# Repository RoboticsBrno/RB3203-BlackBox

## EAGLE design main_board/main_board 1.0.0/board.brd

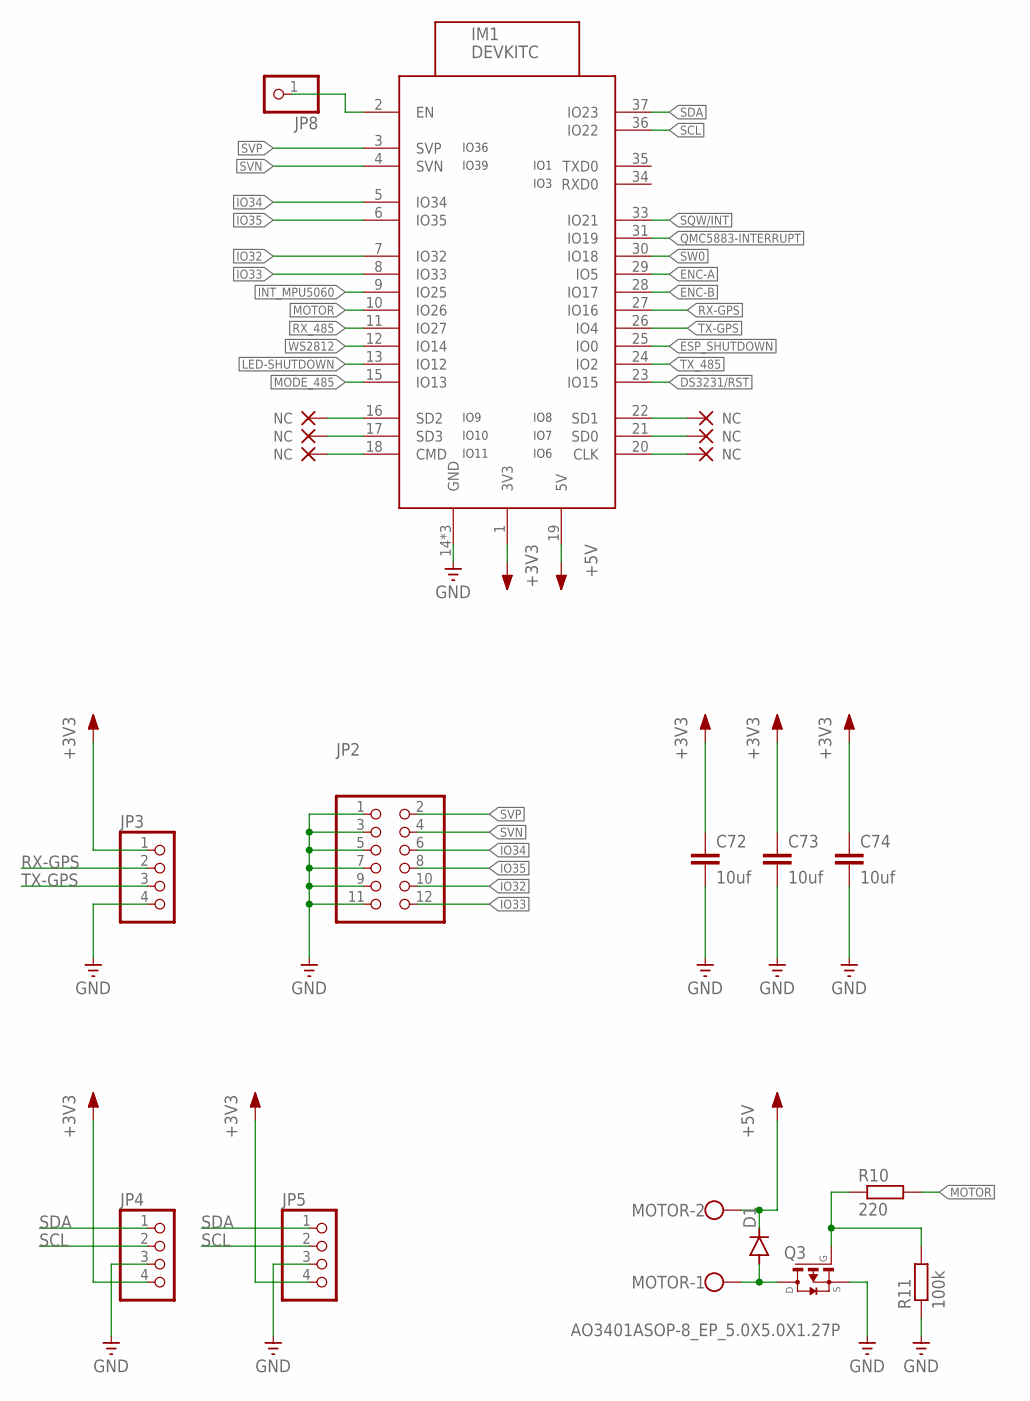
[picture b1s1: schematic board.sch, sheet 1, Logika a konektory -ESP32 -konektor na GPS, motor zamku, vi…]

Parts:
C72, C73, C74: 10uf; C0402
D1: DIODE-DO214BA; DO214BA
IM1: DEVKITC
JP2: PINHD-2X6; 2X06
JP3, JP4, JP5: PINHD-1X4; 1X04
JP8: PINHD-1X1; 1X01
MOTOR: W237-102
Q3: AO3401ASOP-8_EP_5.0X5.0X1.27P; SOP-8_EP_5.0X5.0X1.27P
R10: 220; R0402
R11: 100k; R0402

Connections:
+3V3: C72.1, C73.1, C74.1, IM1.1 (3V3), JP3.1, JP4.4, JP5.4; also elsewhere on the board
+5V: D1.C, IM1.19 (5V), MOTOR.2; also elsewhere on the board
DS3231/RST: IM1.23 (IO15); also elsewhere on the board
ENC-A: IM1.29 (IO5); also elsewhere on the board
ENC-B: IM1.28 (IO17); also elsewhere on the board
ESP_SHUTDOWN: IM1.25 (IO0); also elsewhere on the board
GND: C72.2, C73.2, C74.2, IM1.14 (GND), IM1.32 (GND), IM1.38 (GND), JP2.1, JP2.3, JP2.5, JP2.7, JP2.9, JP2.11, JP3.4, JP4.3, JP5.3, Q3.1 (S), Q3.2 (S), Q3.3 (S), R11.1; also elsewhere on the board
INT_MPU5060: IM1.9 (IO25); also elsewhere on the board
IO9_NC: IM1.16 (SD2)
IO9_NC1: IM1.20 (CLK)
IO10_NC: IM1.17 (SD3)
IO10_NC1: IM1.21 (SD0)
IO11_NC: IM1.18 (CMD)
IO11_NC1: IM1.22 (SD1)
IO32: IM1.7 (IO32), JP2.10
IO33: IM1.8 (IO33), JP2.12
IO34: IM1.5 (IO34), JP2.6
IO35: IM1.6 (IO35), JP2.8
LED-SHUTDOWN: IM1.13 (IO12); also elsewhere on the board
MODE_485: IM1.15 (IO13); also elsewhere on the board
MOTOR: IM1.10 (IO26), R10.2
unnamed: D1.A, MOTOR.1, Q3.5 (D), Q3.6 (D), Q3.7 (D), Q3.8 (D), Q3.9 (D)
unnamed: IM1.2 (EN), JP8.1
unnamed: Q3.4 (G), R10.1, R11.2
QMC5883-INTERRUPT: IM1.31 (IO19); also elsewhere on the board
RX-GPS: IM1.27 (IO16), JP3.2
RX_485: IM1.11 (IO27); also elsewhere on the board
SCL: IM1.36 (IO22), JP4.2, JP5.2; also elsewhere on the board
SDA: IM1.37 (IO23), JP4.1, JP5.1; also elsewhere on the board
SQW/INT: IM1.33 (IO21); also elsewhere on the board
SVN: IM1.4 (SVN), JP2.4
SVP: IM1.3 (SVP), JP2.2
SW0: IM1.30 (IO18); also elsewhere on the board
TX-GPS: IM1.26 (IO4), JP3.3
TX_485: IM1.24 (IO2); also elsewhere on the board
WS2812: IM1.12 (IO14); also elsewhere on the board

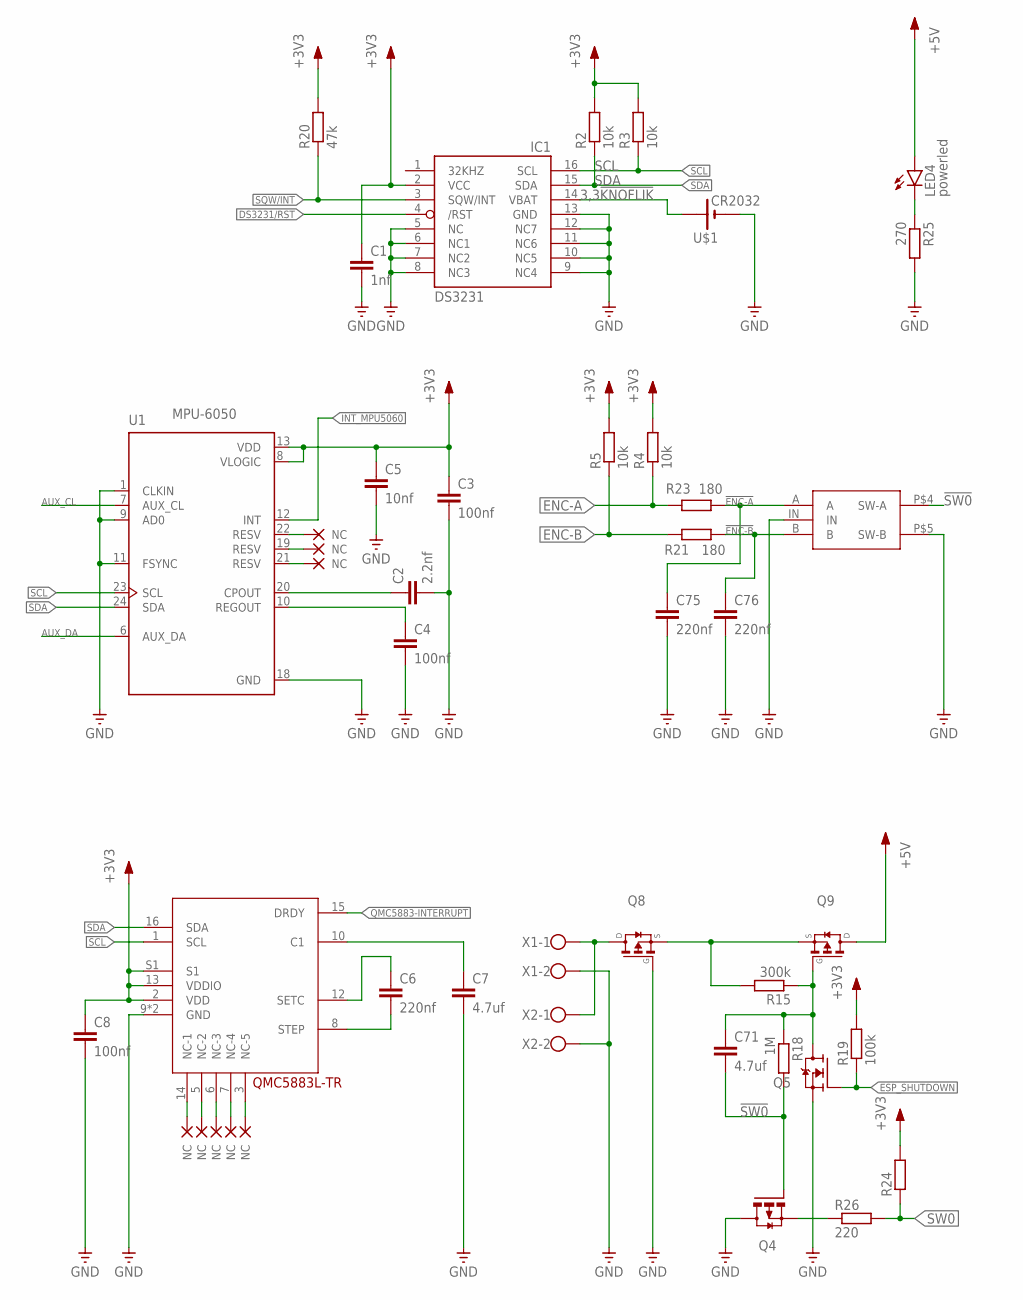
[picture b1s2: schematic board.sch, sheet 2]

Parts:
C1: 1nf; C0402
C2: 2.2nf; C0402
C3: 100nf; C0402
C4: 100nf; C0402K
C5: 10nf; C0402
C6, C75, C76: 220nf; C0402
C7: 4.7uf; C0402
C8: 100nf; C0402P
C71: 4.7uf; C0603
IC1: DS3231/SO; SO16W
IC2: QMC5883L-TR; QMC5882L-TR
LED4: powerled; SML0603
Q4: BSS84; SOT23
Q5: N-MOSFET-SOT23-GSD; SOT23
Q8, Q9: AO3401ASOP-8_EP_5.0X5.0X1.27P; SOP-8_EP_5.0X5.0X1.27P
R2, R3, R4, R5: 10k; R0402
R15: 300k; R0603
R18: 1M; R0603
R19: 100k; R0402
R20, R24: 47k; R0402
R21, R23: 180; R0402
R25: 270; R0402
R26: 220; R0402
U1: MPU-6050; QFN50P400X400X95-24N
U$1: CR2032; CH075
U$62: EC11-1S
X1, X2: W237-102

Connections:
3,3!KNOFLIK: IC1.14 (VBAT), U$1.+
!ENC-A: C75.1, R23.1, U$62.A
!ENC-B: C76.1, R21.1, U$62.B
!SW0: C71.2, Q4.1 (G), R18.2, U$62.P$4 (SW-A)
+3V3: C1.1, C3.1, C5.1, C8.1, IC1.2 (VCC), IC2.2 (VDD), IC2.13 (VDDIO), IC2.S1, R2.2, R3.2, R4.2, R5.2, R19.2, R20.2, R24.2, U1.8 (VLOGIC), U1.13 (VDD); also elsewhere on the board
+5V: LED4.A, Q9.5 (D), Q9.6 (D), Q9.7 (D), Q9.8 (D), Q9.9 (D); also elsewhere on the board
AUX_CL: U1.7 (AUX_CL)
AUX_DA: U1.6 (AUX_DA)
DS3231/RST: IC1.4 (/RST); also elsewhere on the board
ENC-A: R4.1, R23.2; also elsewhere on the board
ENC-B: R5.1, R21.2; also elsewhere on the board
ESP_SHUTDOWN: Q5.1 (G), R19.1; also elsewhere on the board
GND: C1.2, C2.2, C3.2, C4.2, C5.2, C7.2, C8.2, C75.2, C76.2, IC1.5 (NC), IC1.6 (NC1), IC1.7 (NC2), IC1.8 (NC3), IC1.9 (NC4), IC1.10 (NC5), IC1.11 (NC6), IC1.12 (NC7), IC1.13 (GND), IC2.9 (GND), IC2.11 (GND), Q4.3 (D), Q5.2 (S), Q8.4 (G), R25.2, U1.1 (CLKIN), U1.9 (AD0), U1.11 (FSYNC), U1.18 (GND), U$1.-, U$62.IN, U$62.P$5 (SW-B), X1.2, X2.2; also elsewhere on the board
INT_MPU5060: U1.12 (INT); also elsewhere on the board
IO9_NC2: IC2.5 (NC-2)
IO9_NC3: IC2.14 (NC-1)
IO9_NC4: U1.19 (RESV)
IO9_NC5: U1.21 (RESV)
IO9_NC6: IC2.3 (NC-5)
IO9_NC7: IC2.7 (NC-4)
IO10_NC2: IC2.6 (NC-3)
IO10_NC4: U1.22 (RESV)
LED4: LED4.C, R25.1
unnamed: C2.1, U1.20 (CPOUT)
unnamed: C4.1, U1.10 (REGOUT)
unnamed: Q8.5 (D), Q8.6 (D), Q8.7 (D), Q8.8 (D), Q8.9 (D), X1.1, X2.1
unnamed: Q8.1 (S), Q8.2 (S), Q8.3 (S), Q9.1 (S), Q9.2 (S), Q9.3 (S), R15.2
unnamed: C71.1, Q5.3 (D), Q9.4 (G), R15.1, R18.1
unnamed: Q4.2 (S), R26.1
unnamed: C6.1, IC2.12 (SETC)
unnamed: C6.2, IC2.8 (STEP)
unnamed: C7.1, IC2.10 (C1)
QMC5883-INTERRUPT: IC2.15 (DRDY); also elsewhere on the board
SCL: IC1.16 (SCL), IC2.1 (SCL), R3.1, U1.23 (SCL); also elsewhere on the board
SDA: IC1.15 (SDA), IC2.16 (SDA), R2.1, U1.24 (SDA); also elsewhere on the board
SQW/INT: IC1.3 (SQW/INT), R20.1; also elsewhere on the board
SW0: R24.1, R26.2; also elsewhere on the board

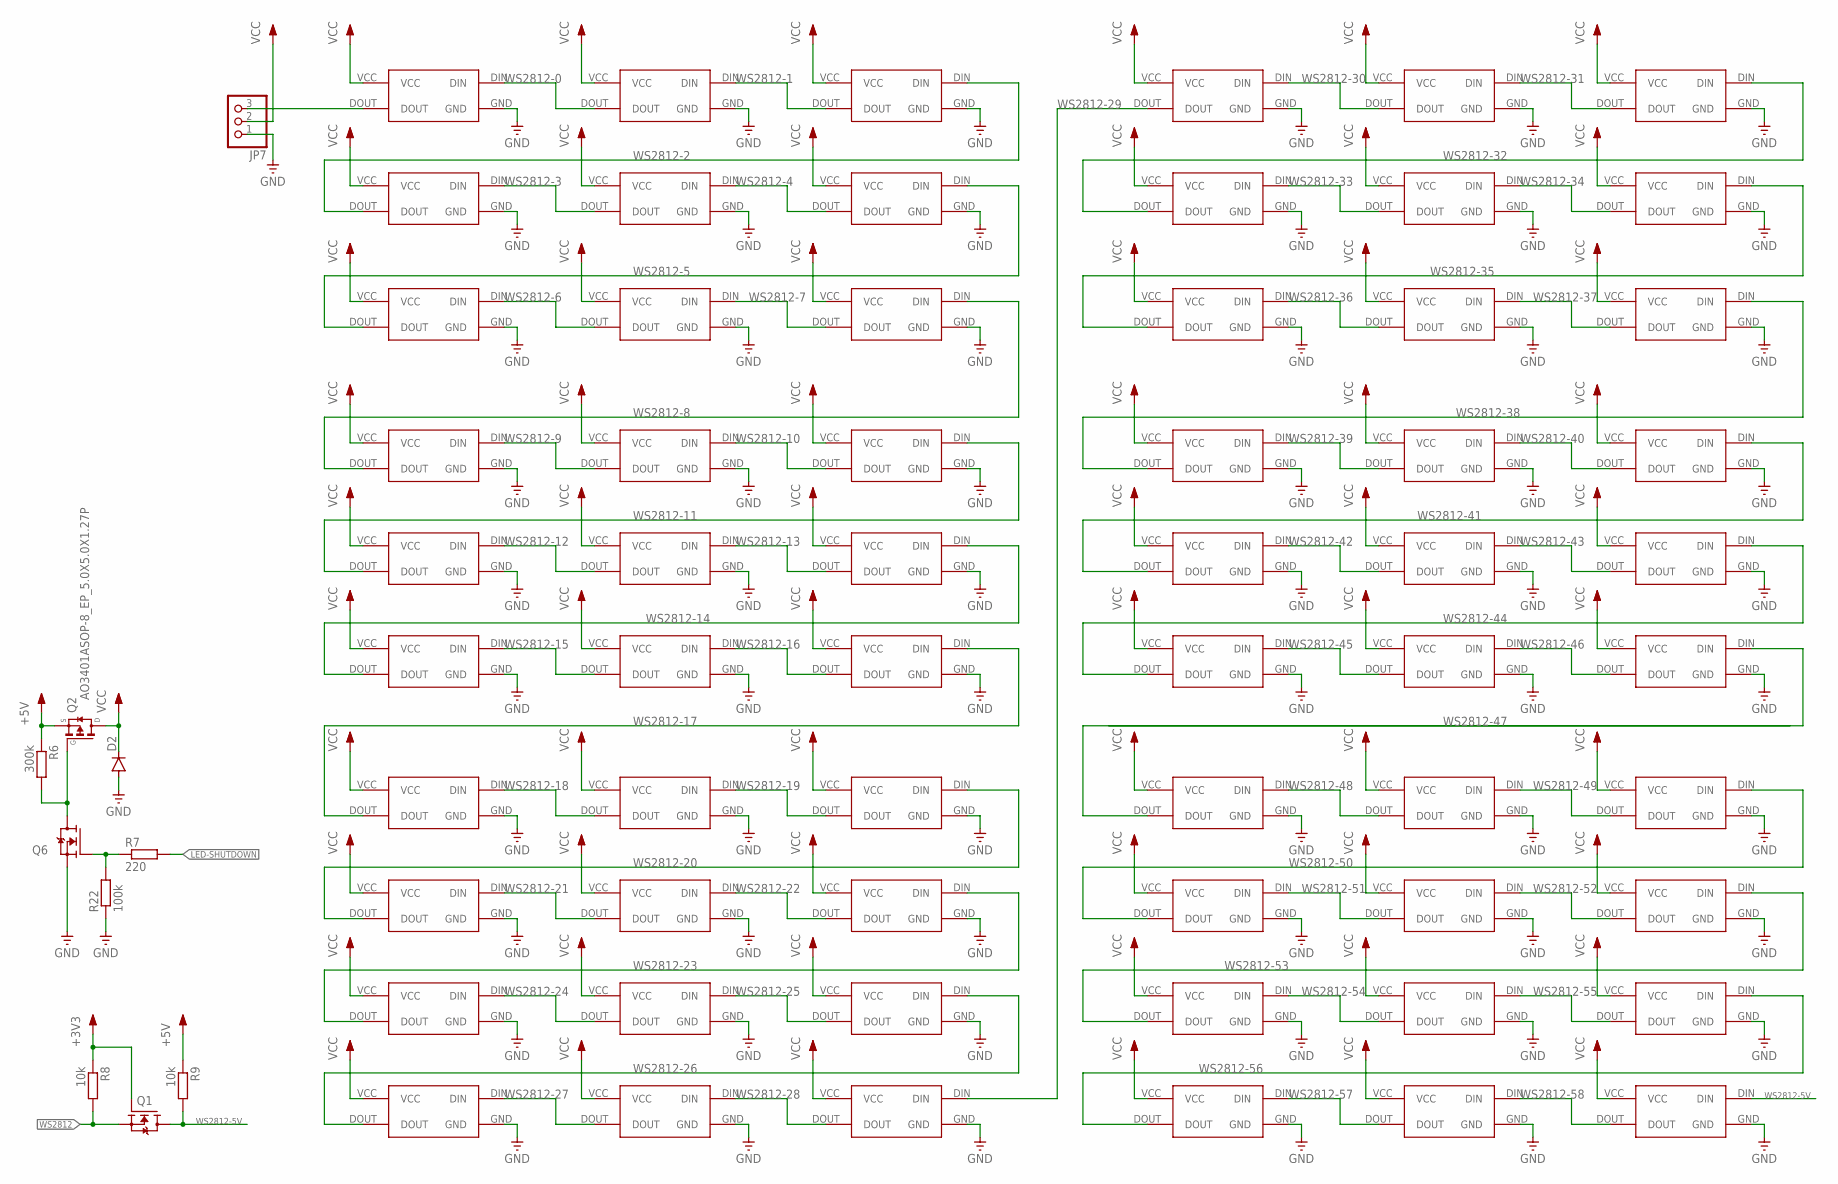
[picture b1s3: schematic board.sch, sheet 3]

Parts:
D2: DIODE-DO214BA; DO214BA
JP7: PINHD-1X3; 1X03
Q1, Q6: N-MOSFET-SOT23-GSD; SOT23
Q2: AO3401ASOP-8_EP_5.0X5.0X1.27P; SOP-8_EP_5.0X5.0X1.27P
R6: 300k; R0402
R7: 220; R0402
R8, R9: 10k; R0402
R22: 100k; R0402
U$2, U$3, U$4, U$5, U$6, U$7, U$8, U$9, U$10, U$11, U$12, U$13, U$14, U$15, U$16, U$17, U$18, U$19, U$20, U$21, U$22, U$23, U$24, U$25, U$26, U$27, U$28, U$29, U$30, U$31, U$32, U$33, U$34, U$35, U$36, U$37, U$38, U$39, U$40, U$41, U$42, U$43, U$44, U$45, U$46, U$47, U$48, U$49, U$50, U$51, U$52, U$53, U$54, U$55, U$56, U$57, U$58, U$59, U$60, U$61: WS2812; WS2812B-MINI

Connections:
+3V3: Q1.1 (G), R8.1; also elsewhere on the board
+5V: Q2.1 (S), Q2.2 (S), Q2.3 (S), R6.1, R9.1; also elsewhere on the board
GND: D2.A, JP7.1, Q6.2 (S), R22.1, U$2.GND, U$3.GND, U$4.GND, U$5.GND, U$6.GND, U$7.GND, U$8.GND, U$9.GND, U$10.GND, U$11.GND, U$12.GND, U$13.GND, U$14.GND, U$15.GND, U$16.GND, U$17.GND, U$18.GND, U$19.GND, U$20.GND, U$21.GND, U$22.GND, U$23.GND, U$24.GND, U$25.GND, U$26.GND, U$27.GND, U$28.GND, U$29.GND, U$30.GND, U$31.GND, U$32.GND, U$33.GND, U$34.GND, U$35.GND, U$36.GND, U$37.GND, U$38.GND, U$39.GND, U$40.GND, U$41.GND, U$42.GND, U$43.GND, U$44.GND, U$45.GND, U$46.GND, U$47.GND, U$48.GND, U$49.GND, U$50.GND, U$51.GND, U$52.GND, U$53.GND, U$54.GND, U$55.GND, U$56.GND, U$57.GND, U$58.GND, U$59.GND, U$60.GND, U$61.GND; also elsewhere on the board
LED-SHUTDOWN: R7.2; also elsewhere on the board
unnamed: JP7.3, U$2.DOUT
unnamed: U$49.DIN, U$50.DOUT
unnamed: Q2.4 (G), Q6.3 (D), R6.2
unnamed: Q6.1 (G), R7.1, R22.2
VCC: D2.C, JP7.2, Q2.5 (D), Q2.6 (D), Q2.7 (D), Q2.8 (D), Q2.9 (D), U$2.VCC, U$3.VCC, U$4.VCC, U$5.VCC, U$6.VCC, U$7.VCC, U$8.VCC, U$9.VCC, U$10.VCC, U$11.VCC, U$12.VCC, U$13.VCC, U$14.VCC, U$15.VCC, U$16.VCC, U$17.VCC, U$18.VCC, U$19.VCC, U$20.VCC, U$21.VCC, U$22.VCC, U$23.VCC, U$24.VCC, U$25.VCC, U$26.VCC, U$27.VCC, U$28.VCC, U$29.VCC, U$30.VCC, U$31.VCC, U$32.VCC, U$33.VCC, U$34.VCC, U$35.VCC, U$36.VCC, U$37.VCC, U$38.VCC, U$39.VCC, U$40.VCC, U$41.VCC, U$42.VCC, U$43.VCC, U$44.VCC, U$45.VCC, U$46.VCC, U$47.VCC, U$48.VCC, U$49.VCC, U$50.VCC, U$51.VCC, U$52.VCC, U$53.VCC, U$54.VCC, U$55.VCC, U$56.VCC, U$57.VCC, U$58.VCC, U$59.VCC, U$60.VCC, U$61.VCC; also elsewhere on the board
WS2812: Q1.2 (S), R8.2; also elsewhere on the board
WS2812-0: U$2.DIN, U$3.DOUT
WS2812-1: U$3.DIN, U$4.DOUT
WS2812-2: U$4.DIN, U$5.DOUT
WS2812-3: U$5.DIN, U$6.DOUT
WS2812-4: U$6.DIN, U$7.DOUT
WS2812-5: U$7.DIN, U$8.DOUT
WS2812-5V: Q1.3 (D), R9.2, U$61.DIN
WS2812-6: U$8.DIN, U$9.DOUT
WS2812-7: U$9.DIN, U$10.DOUT
WS2812-8: U$10.DIN, U$11.DOUT
WS2812-9: U$11.DIN, U$12.DOUT
WS2812-10: U$12.DIN, U$13.DOUT
WS2812-11: U$13.DIN, U$14.DOUT
WS2812-12: U$14.DIN, U$15.DOUT
WS2812-13: U$15.DIN, U$16.DOUT
WS2812-14: U$16.DIN, U$17.DOUT
WS2812-15: U$17.DIN, U$18.DOUT
WS2812-16: U$18.DIN, U$19.DOUT
WS2812-17: U$19.DIN, U$20.DOUT
WS2812-18: U$20.DIN, U$21.DOUT
WS2812-19: U$21.DIN, U$22.DOUT
WS2812-20: U$22.DIN, U$23.DOUT
WS2812-21: U$23.DIN, U$24.DOUT
WS2812-22: U$24.DIN, U$25.DOUT
WS2812-23: U$25.DIN, U$26.DOUT
WS2812-24: U$26.DIN, U$27.DOUT
WS2812-25: U$27.DIN, U$28.DOUT
WS2812-26: U$28.DIN, U$29.DOUT
WS2812-27: U$29.DIN, U$30.DOUT
WS2812-28: U$30.DIN, U$31.DOUT
WS2812-29: U$31.DIN, U$32.DOUT
WS2812-30: U$32.DIN, U$33.DOUT
WS2812-31: U$33.DIN, U$34.DOUT
WS2812-32: U$34.DIN, U$35.DOUT
WS2812-33: U$35.DIN, U$36.DOUT
WS2812-34: U$36.DIN, U$37.DOUT
WS2812-35: U$37.DIN, U$38.DOUT
WS2812-36: U$38.DIN, U$39.DOUT
WS2812-37: U$39.DIN, U$40.DOUT
WS2812-38: U$40.DIN, U$41.DOUT
WS2812-39: U$41.DIN, U$42.DOUT
WS2812-40: U$42.DIN, U$43.DOUT
WS2812-41: U$43.DIN, U$44.DOUT
WS2812-42: U$44.DIN, U$45.DOUT
WS2812-43: U$45.DIN, U$46.DOUT
WS2812-44: U$46.DIN, U$47.DOUT
WS2812-45: U$47.DIN, U$48.DOUT
WS2812-46: U$48.DIN, U$49.DOUT
WS2812-48: U$50.DIN, U$51.DOUT
WS2812-49: U$51.DIN, U$52.DOUT
WS2812-50: U$52.DIN, U$53.DOUT
WS2812-51: U$53.DIN, U$54.DOUT
WS2812-52: U$54.DIN, U$55.DOUT
WS2812-53: U$55.DIN, U$56.DOUT
WS2812-54: U$56.DIN, U$57.DOUT
WS2812-55: U$57.DIN, U$58.DOUT
WS2812-56: U$58.DIN, U$59.DOUT
WS2812-57: U$59.DIN, U$60.DOUT
WS2812-58: U$60.DIN, U$61.DOUT

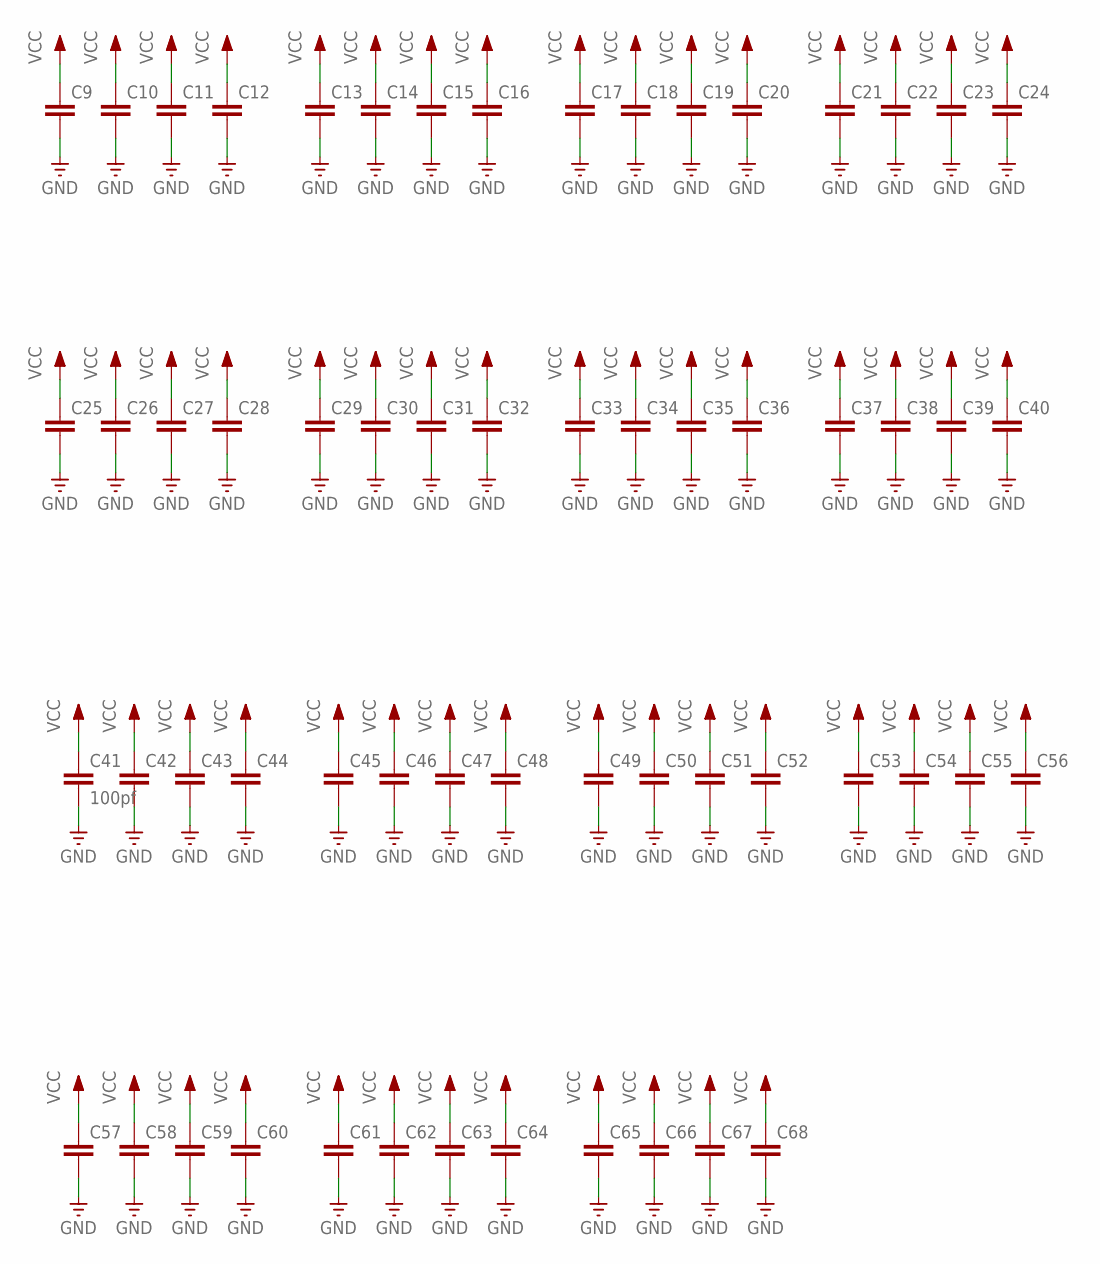
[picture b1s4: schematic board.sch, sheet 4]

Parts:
C9, C10, C11, C12, C13, C14, C15, C16, C17, C18, C19, C20, C21, C22, C23, C24, C25, C26, C27, C28, C29, C30, C31, C32, C33, C34, C35, C36, C37, C38, C39, C40, C42, C43, C44, C45, C46, C47, C48, C49, C50, C51, C52, C53, C54, C55, C56, C57, C58, C59, C60, C61, C62, C63, C64, C65, C66, C67, C68: C-EUC0402; C0402
C41: 100pf; C0402

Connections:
GND: C9.2, C10.2, C11.2, C12.2, C13.2, C14.2, C15.2, C16.2, C17.2, C18.2, C19.2, C20.2, C21.2, C22.2, C23.2, C24.2, C25.2, C26.2, C27.2, C28.2, C29.2, C30.2, C31.2, C32.2, C33.2, C34.2, C35.2, C36.2, C37.2, C38.2, C39.2, C40.2, C41.2, C42.2, C43.2, C44.2, C45.2, C46.2, C47.2, C48.2, C49.2, C50.2, C51.2, C52.2, C53.2, C54.2, C55.2, C56.2, C57.2, C58.2, C59.2, C60.2, C61.2, C62.2, C63.2, C64.2, C65.2, C66.2, C67.2, C68.2; also elsewhere on the board
VCC: C9.1, C10.1, C11.1, C12.1, C13.1, C14.1, C15.1, C16.1, C17.1, C18.1, C19.1, C20.1, C21.1, C22.1, C23.1, C24.1, C25.1, C26.1, C27.1, C28.1, C29.1, C30.1, C31.1, C32.1, C33.1, C34.1, C35.1, C36.1, C37.1, C38.1, C39.1, C40.1, C41.1, C42.1, C43.1, C44.1, C45.1, C46.1, C47.1, C48.1, C49.1, C50.1, C51.1, C52.1, C53.1, C54.1, C55.1, C56.1, C57.1, C58.1, C59.1, C60.1, C61.1, C62.1, C63.1, C64.1, C65.1, C66.1, C67.1, C68.1; also elsewhere on the board

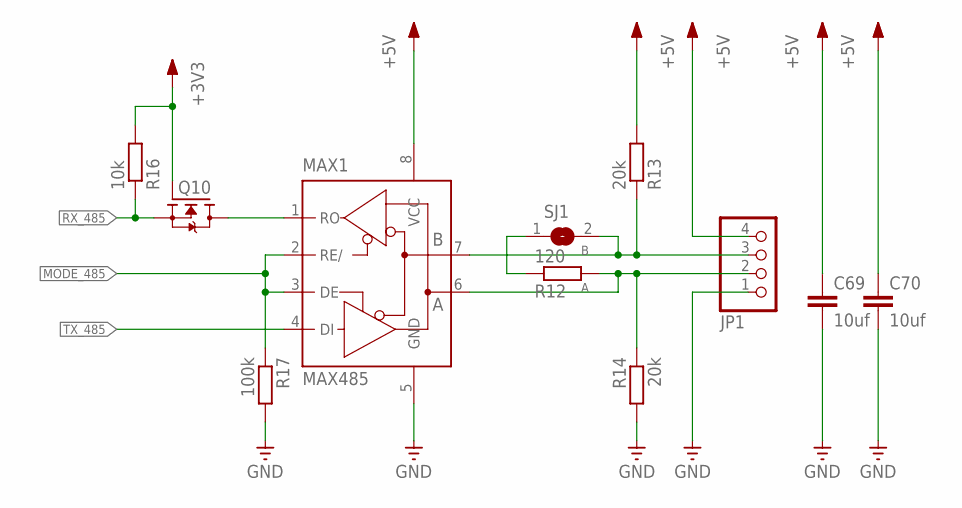
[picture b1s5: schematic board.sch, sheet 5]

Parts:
C69, C70: 10uf; C0402K
JP1: PINHD-1X4; 1X04
MAX1: MAX485; SO08
Q10: N-MOSFET-SOT23-GSD; SOT23
R12: 120; R0402
R13, R14: 20k; R0402
R16: 10k; R0402
R17: 100k; R0402
SJ1: SJ

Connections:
+3V3: Q10.1 (G), R16.2; also elsewhere on the board
+5V: C69.1, C70.1, JP1.4, MAX1.8 (VCC), R13.2; also elsewhere on the board
A: JP1.2, MAX1.6 (A), R12.2, R14.1
B: JP1.3, MAX1.7 (B), R13.1, SJ1.2
GND: C69.2, C70.2, JP1.1, MAX1.5 (GND), R14.2, R17.2; also elsewhere on the board
MODE_485: MAX1.2 (RE/), MAX1.3 (DE), R17.1; also elsewhere on the board
unnamed: R12.1, SJ1.1
RX-485-5V: MAX1.1 (RO), Q10.3 (D)
RX_485: Q10.2 (S), R16.1; also elsewhere on the board
TX_485: MAX1.4 (DI); also elsewhere on the board

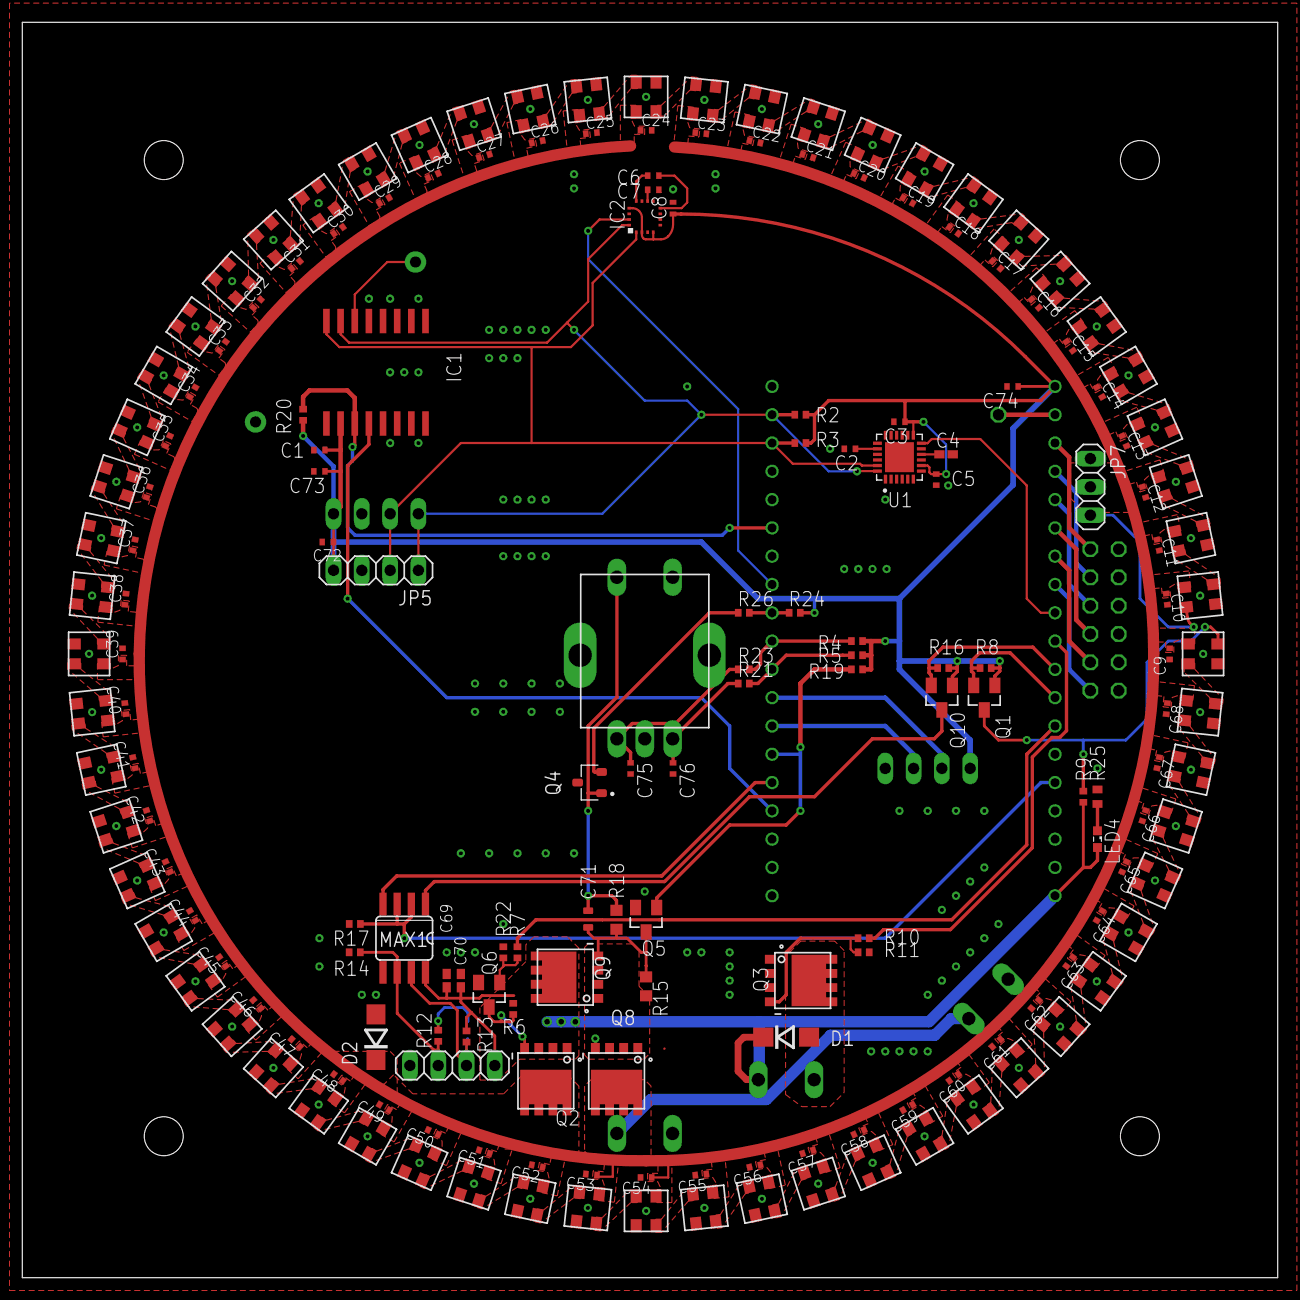
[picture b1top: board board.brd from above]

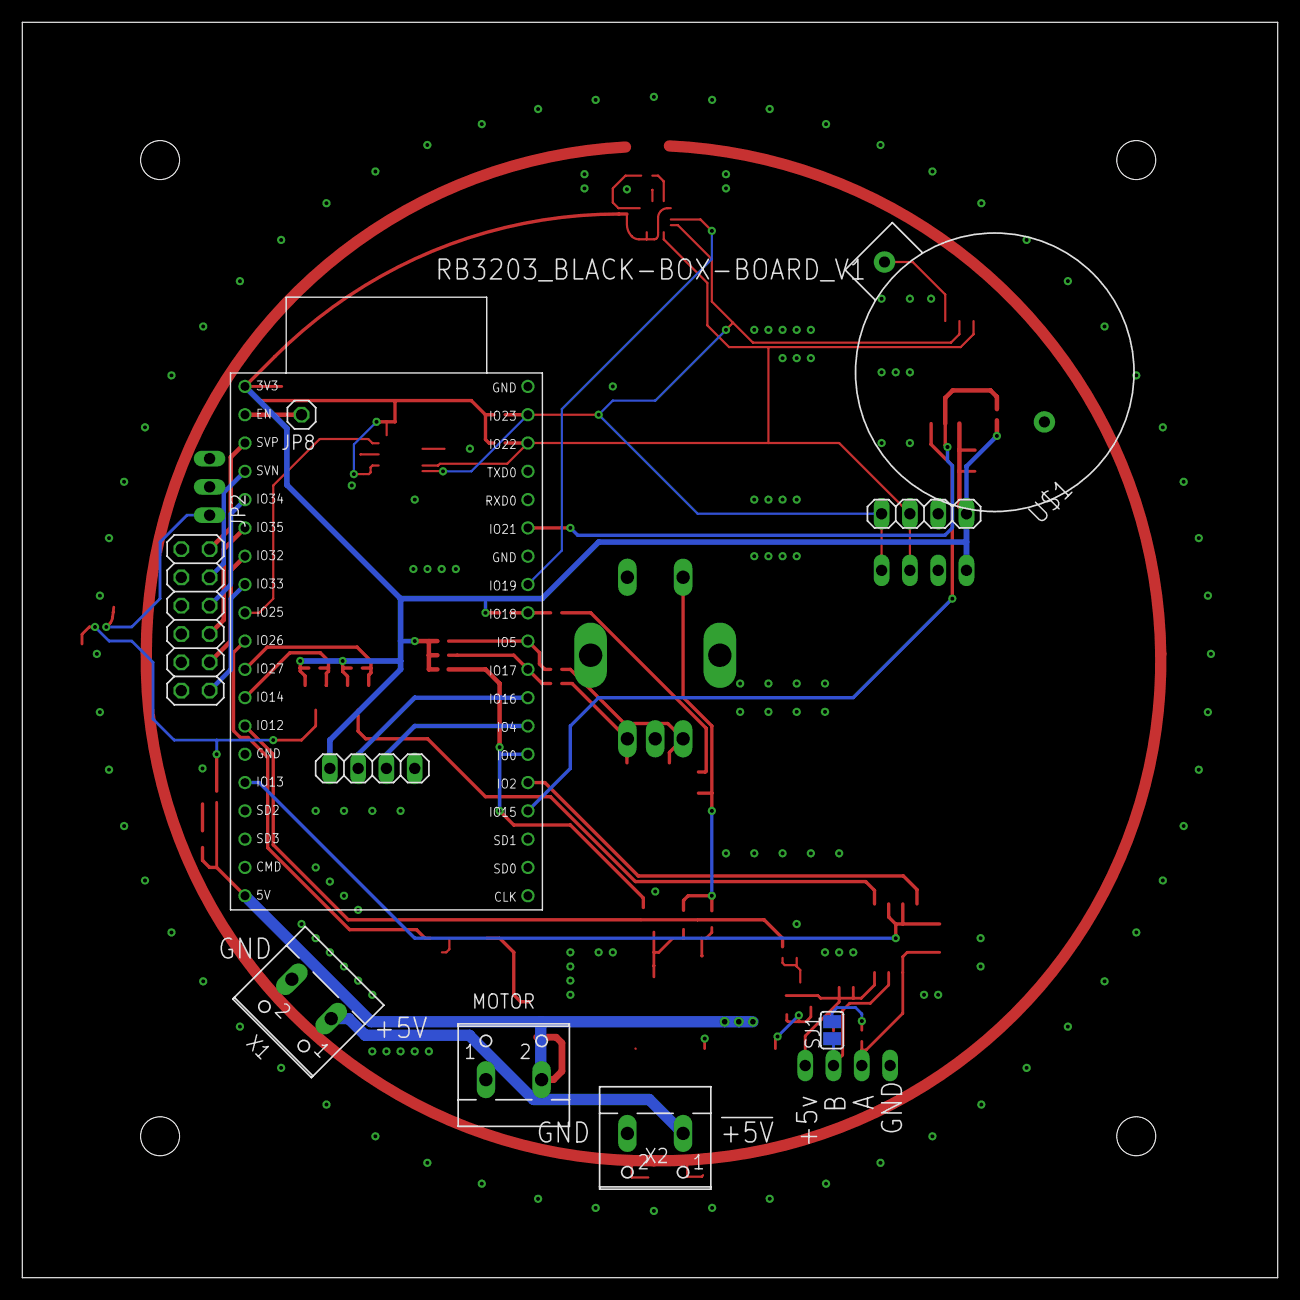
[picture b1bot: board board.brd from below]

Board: 2 copper layers, 112.7 x 112.7 mm, 191 parts (10 on the bottom side), 112 nets.

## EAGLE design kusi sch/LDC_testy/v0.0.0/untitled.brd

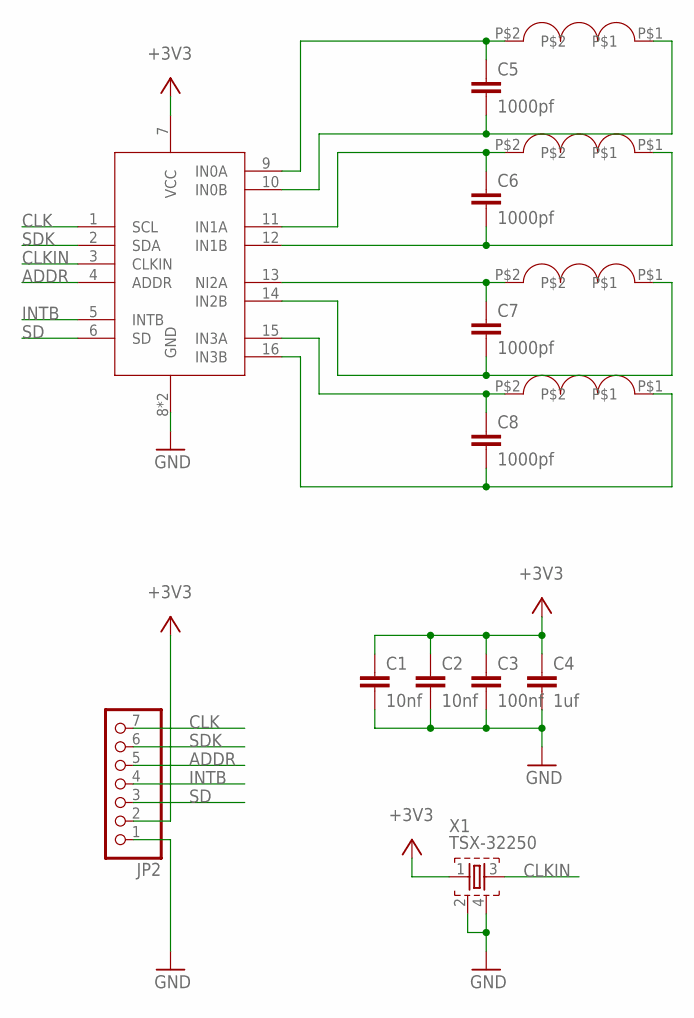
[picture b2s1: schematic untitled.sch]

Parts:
C1, C2: 10nf; C0603
C3: 100nf; C0603
C4: 1uf; C0603
C5, C6, C7, C8: 1000pf; C0603
JP2: PINHD-1X7; 1X07
U$1: LDC1314; QFN50P400X400X80-17N
U$2, U$3, U$4, U$5: COIL; L19.18.2
X1: TSX-32250; TSX-3225

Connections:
+3V3: C1.1, C2.1, C3.1, C4.1, JP2.2, U$1.7 (VCC), X1.1
ADDR: JP2.5, U$1.4 (ADDR)
CLK: JP2.7, U$1.1 (SCL)
CLKIN: U$1.3 (CLKIN), X1.3
GND: C1.2, C2.2, C3.2, C4.2, JP2.1, U$1.8 (GND), U$1.17 (GND), X1.2, X1.4
INTB: JP2.4, U$1.5 (INTB)
unnamed: C5.2, U$1.10 (IN0B), U$2.P$1
unnamed: C6.2, U$1.12 (IN1B), U$3.P$1
unnamed: C7.2, U$1.14 (IN2B), U$4.P$1
unnamed: C8.2, U$1.16 (IN3B), U$5.P$1
unnamed: C5.1, U$1.9 (IN0A), U$2.P$2
unnamed: C6.1, U$1.11 (IN1A), U$3.P$2
unnamed: C7.1, U$1.13 (NI2A), U$4.P$2
unnamed: C8.1, U$1.15 (IN3A), U$5.P$2
SD: JP2.3, U$1.6 (SD)
SDK: JP2.6, U$1.2 (SDA)

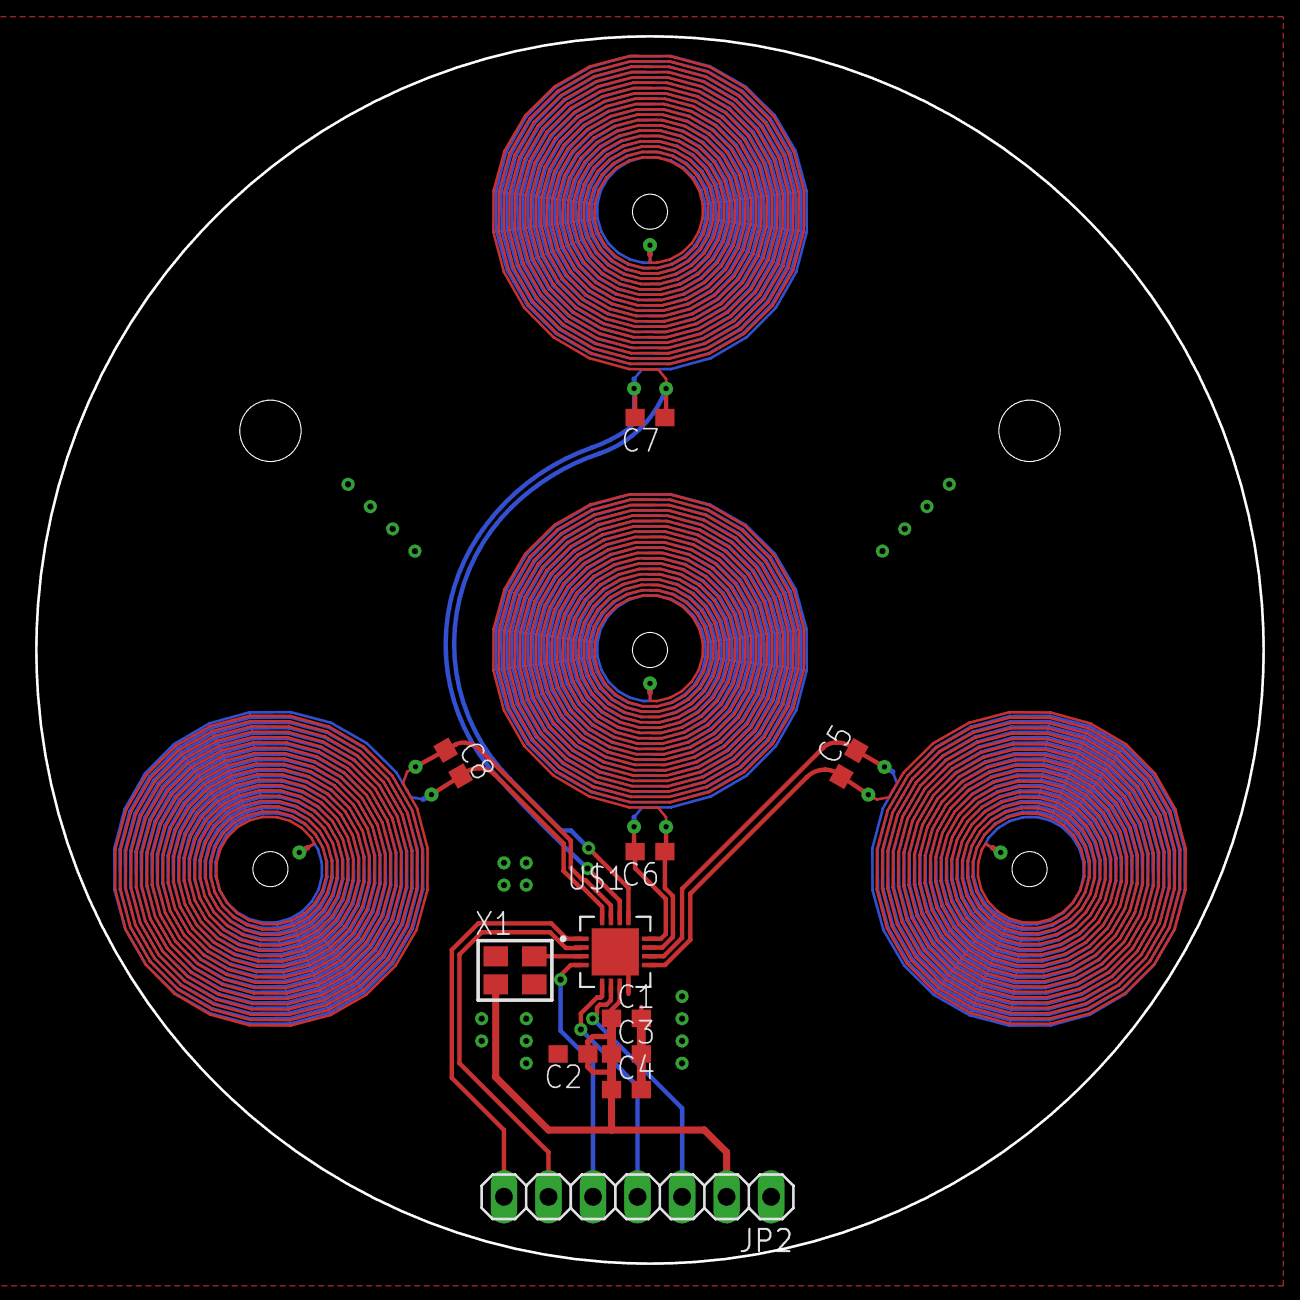
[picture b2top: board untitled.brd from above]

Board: 2 copper layers, 70.0 x 70.0 mm, 15 parts (0 on the bottom side), 16 nets.

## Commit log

2020-03-01 presun_do_solo_repozitare
2020-03-01 utrizeni
2020-10-04 LD_test
2020-10-06 KiCad-import
2020-10-27 New_B.B
    New schematic in KiCad.
    -ESP32 wrover
    + ESP32 have programer (CP3202) on board
    + CP3202 is consumed current only if USB is plug in
    -A9G
    + GPS, GPAR
2020-10-30 IR+ENC
2020-11-07 konzultace_s_Kubou_01
2020-11-07 pull_up(WS2812_power+motor)
2020-11-07 interrupt
    all interapt on PCA9555
2020-11-08 preparation_to_drawing_PCB
2020-11-09 complete_preparation_to_drawing_PCB
    footprint for all component and LCSC code for everything for mounting in JLCPCB
2020-11-09 repare last commit
    i forgot to save some footprint in last commit
2020-11-09 optimalizace_kondenzatoru
2020-11-12 start vith pcb
    firsxxt proposal component layout of main board
2020-11-15 orezavani
    smazaní A9G, SD karty, a zvuku
2020-11-17 nabijecka
2020-11-17 odpojovan_nabijecky
2020-11-21 18650
2020-11-28 polifuse
    -filtr k prijmaci IR
    -merwni bterky -> za zapinani
    -odstraneni odpojovani nabijecky + oprava napajeciho prouhu
    -odstraneni prevodniku napeti k WS2812
2020-11-28 PCB-0,1
2020-12-06 napajeni_na_stejne_strane
    -poradi na konektoru
    -napajeni IR prijmece z 5V na VCC
    -vyssi nabijeci proud
    -WS2812_power na IO21
2020-12-06 lenky_k_CP2102
2020-12-11 uvolneni enkoderu
    - dolomitelny enkoder
    - zmenseni via u civek LDC
    - vymena pouzdra USB-C
    - otoceni IR prijmace
    - zakas vylivani medi pod BMX9555
    - odstraneni "ochrannych" odporu k M41T62
2020-12-15 popisky
    -popisky
    -poladeni uddeleni enkoderu
    -poladeni nayvu drah
    -priopjeni gnd USB
    -poligon V5 na led-desce do spodni vrstvu
2020-12-16 LDC footprint
    prodlouzeni pedu pro usnadneni rucniho osazovani
2020-12-21 JLCdata
    - korekce pozice a natoceni
    - data pro vyrobu
2021-02-02 slozka_V1
2021-02-02 upravy_pouzder
2021-02-02 wrover
2021-02-02 opravi_a_dodatky MPU/QMC/conn_A9G
2021-02-02 podklady_a_modeli_3D_modelu
2021-04-07 opravy_a_dodatky_2
2021-05-18 lucerna
2021-05-19 posouvani-LCSC
2021-05-21 presuny_konektoru
2021-05-25 new schema
2021-05-25 spinana nabijecka a FT232 pcb
2021-05-26 vymena rezistoru pro snimani nabijeciho proudu
2021-06-21 touchboard-connectLed-isteni
2022-11-12 Outline schematic of the new lantern version
    Division into four PCB (PressPad , LEDBoard, MainBoard and bottom ServoButtonBoard)
    Equipmant:
    PressPad - NFC coil and LDC targets
    LEDBoard - 60 LEDs circle with output conector, LDC and his coil, NFC chip M24SR64
    MainBoard - ESP32 WROVER with CP2102 USB to UART convertor, PowerControler (two chargers TP5100 for charging four bateris 18650, linear regulator for 3V3 branch and stepup for 5V branch, main power s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
    ServoBoard - pin expander CY8C9520A and conectors
2023-03-16 Tests
2023-07-21 Establishment of the Kicadi Project
2023-07-21 clean
2023-07-23 Two 5V brange with automatic shutdown step-up
2023-07-23 Simplify of automatic shutdown step-up
2023-07-29 5V branch

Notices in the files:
parts and their libraries:
esp32: Creative Commons Attribution-ShareAlike 4.0 International
